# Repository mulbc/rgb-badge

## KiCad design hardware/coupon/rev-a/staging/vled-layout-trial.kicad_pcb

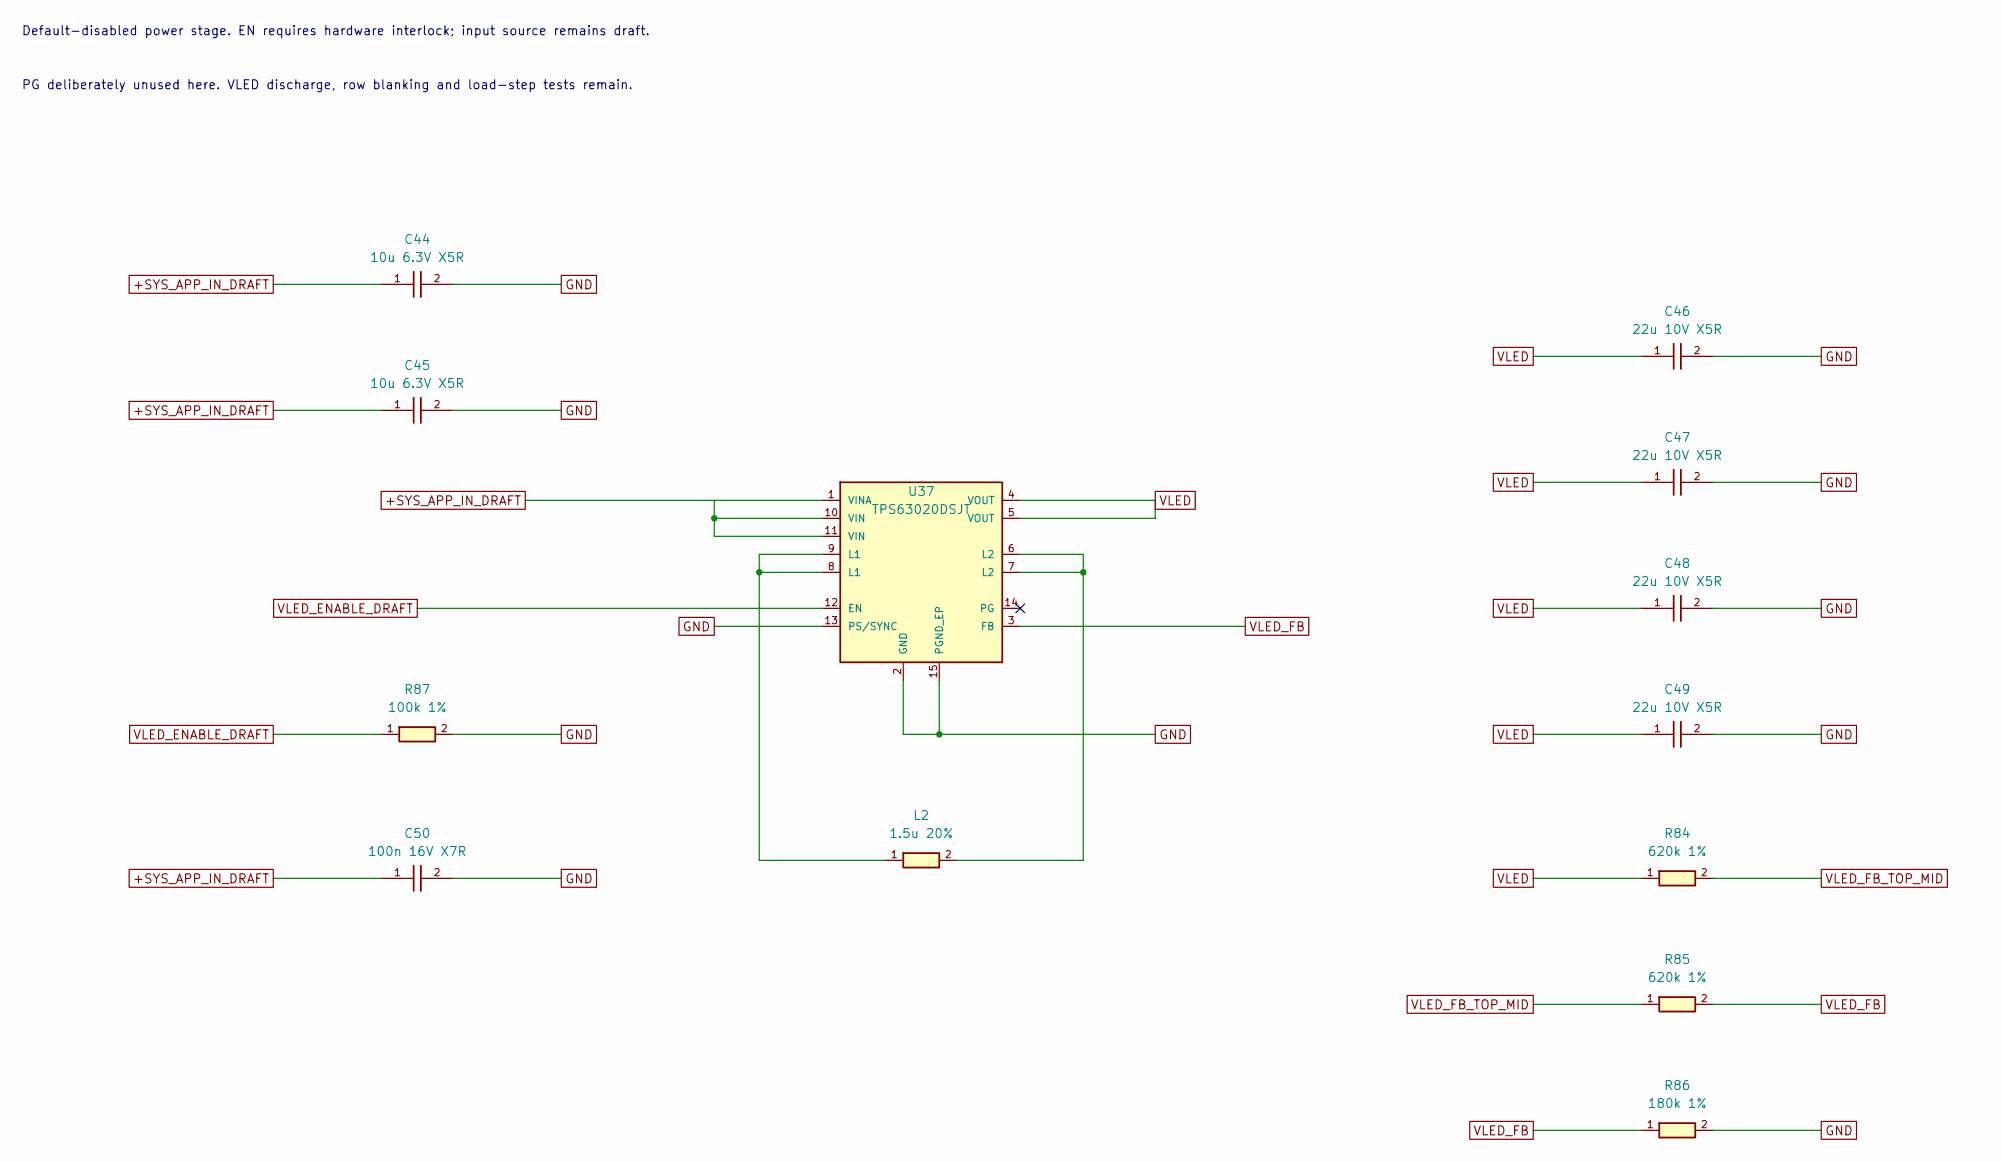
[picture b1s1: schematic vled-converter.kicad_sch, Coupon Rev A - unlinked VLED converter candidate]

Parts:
C44, C45: 10u 6.3V X5R; C_Murata_GRM18_0603; MPN GRM188R60J106ME47D
C46, C47, C48, C49: 22u 10V X5R; C_Murata_GRM18_0603; MPN GRM187R61A226ME15
C50: 100n 16V X7R; C_Murata_GRM15_0402; MPN GRM155R71C104KA88D
L2: 1.5u 20%; L_Murata_DFE252012P; MPN DFE252012P-1R5M=P2
R84, R85: 620k 1%; R_Panasonic_ERJ2_0402; MPN ERJ2RKF6203X
R86: 180k 1%; R_Panasonic_ERJ2_0402; MPN ERJ2RKF1803X
R87: 100k 1%; R_Panasonic_ERJ2_0402; MPN ERJ2RKF1003X
U37: TPS63020DSJT; VSON_TI_DSJ0014_4x3mm_P0.5mm_EP2.85x1.58mm; MPN TPS63020DSJT

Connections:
+SYS_APP_IN_DRAFT: C44.1, C45.1, C50.1, U37.1 (VINA), U37.10 (VIN), U37.11 (VIN)
GND: C44.2, C45.2, C46.2, C47.2, C48.2, C49.2, C50.2, R86.2, R87.2, U37.2 (GND), U37.13 (PS/SYNC), U37.15 (PGND_EP)
unnamed: L2.1, U37.8 (L1), U37.9 (L1)
unnamed: L2.2, U37.6 (L2), U37.7 (L2)
VLED: C46.1, C47.1, C48.1, C49.1, R84.1, U37.4 (VOUT), U37.5 (VOUT)
VLED_ENABLE_DRAFT: R87.1, U37.12 (EN)
VLED_FB: R85.2, R86.1, U37.3 (FB)
VLED_FB_TOP_MID: R84.2, R85.1

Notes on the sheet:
Default-disabled power stage. EN requires hardware interlock; input source remains draft.
PG deliberately unused here. VLED discharge, row blanking and load-step tests remain.

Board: 2 copper layers, 13 parts (0 on the bottom side), 8 nets, no tracks yet.

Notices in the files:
parts and their libraries:
GRM18 0603 reflow land pattern, midpoint of Murata recommended ranges; SPDX-License-Identifier: CERN-OHL-S-2.0
Manufacturer range-based reflow land pattern; SPDX-License-Identifier: CERN-OHL-S-2.0
